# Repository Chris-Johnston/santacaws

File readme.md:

# Santa CAWs

More novelty circuitboards, powered by an ATTINY404.

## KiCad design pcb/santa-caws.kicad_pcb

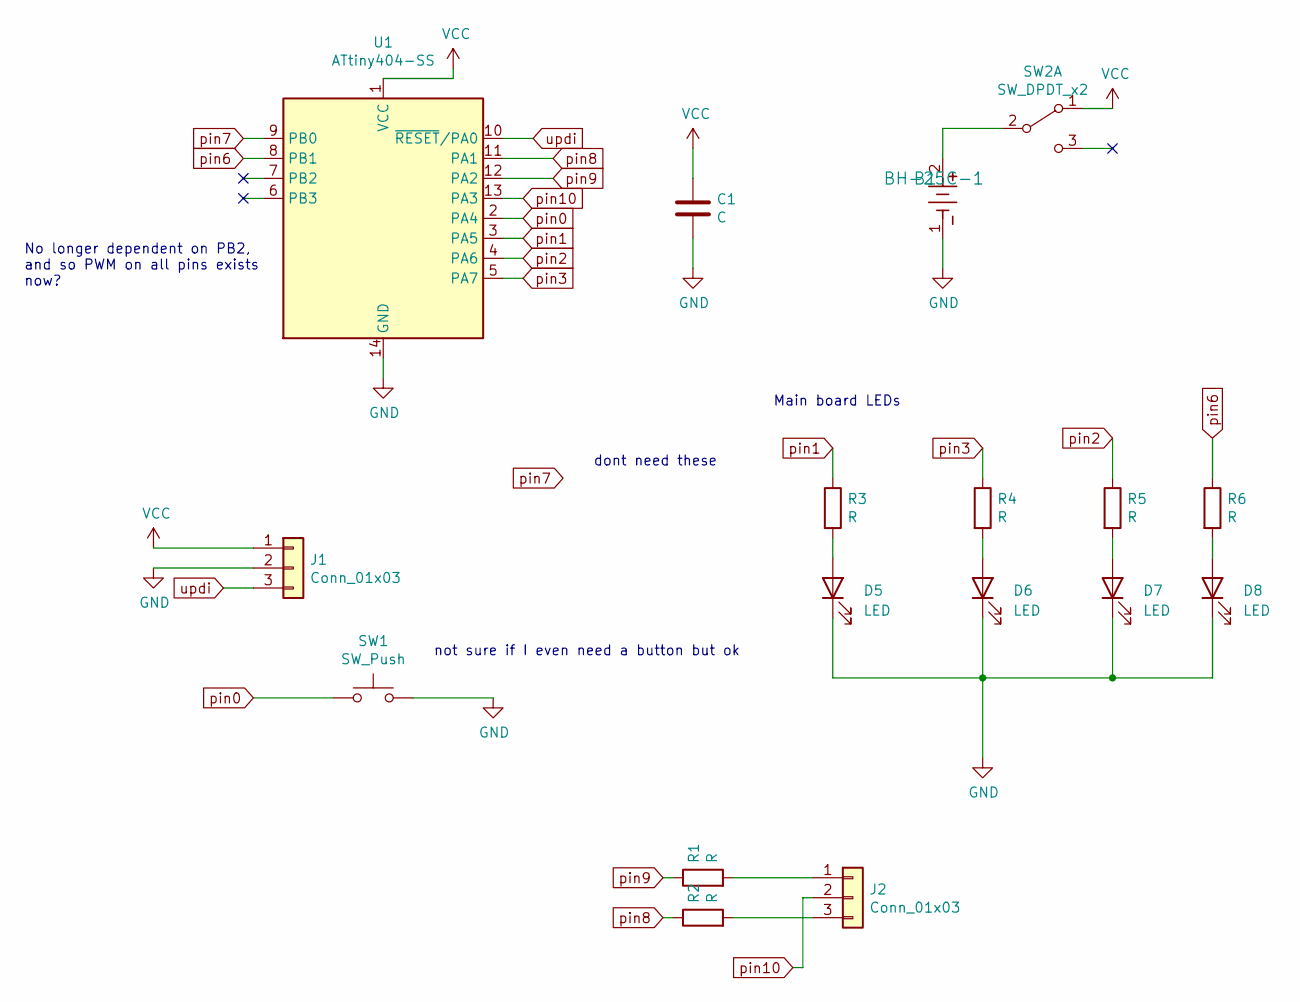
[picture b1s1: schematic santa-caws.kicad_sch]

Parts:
B1: BH-25C-1; BH-25C-1_ADM
C1: C; C_1206_3216Metric_Pad1.33x1.80mm_HandSolder
D5, D6, D7, D8: LED; Custom_LessSilkscreenLED_1206_3216Metric_Pad1.42x1.75mm_Han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
J1: Conn_01x03; custom_updipad_PinHeader_1x03_P2.54mm_Vertical
J2: Conn_01x03; PinSocket_1x03_P2.54mm_Horizontal
R1, R2, R3, R4, R5, R6: R; R_1206_3216Metric_Pad1.30x1.75mm_HandSolder
SW1: SW_Push; SW_Push_1P1T_NO_6x6mm_H9.5mm
SW2: SW_DPDT_x2; SW_SPDT_CK-JS102011SAQN
U1: ATtiny404-SS; SOIC-14_3.9x8.7mm_P1.27mm

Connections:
GND: B1.1, C1.2, D5.1 (K), D6.1 (K), D7.1 (K), D8.1 (K), J1.2, SW1.2, U1.14 (GND)
unnamed: B1.2, SW2.2 (B)
unnamed: D5.2 (A), R3.2
unnamed: D6.2 (A), R4.2
unnamed: D7.2 (A), R5.2
unnamed: D8.2 (A), R6.2
unnamed: J2.1, R1.2
unnamed: J2.3, R2.2
VCC: C1.1, J1.1, SW2.1 (A), U1.1 (VCC)
pin0: SW1.1, U1.2 (PA4)
pin1: R3.1, U1.3 (PA5)
pin2: R5.1, U1.4 (PA6)
pin3: R4.1, U1.5 (PA7)
pin6: R6.1, U1.8 (PB1)
pin7: U1.9 (PB0)
pin8: R2.1, U1.11 (PA1)
pin9: R1.1, U1.12 (PA2)
pin10: J2.2, U1.13 (PA3)
updi: J1.3, U1.10 (~RESET/PA0)

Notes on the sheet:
not sure if I even need a button but ok
No longer dependent on PB2, and so PWM on all pins exists now?
dont need these
Main board LEDs

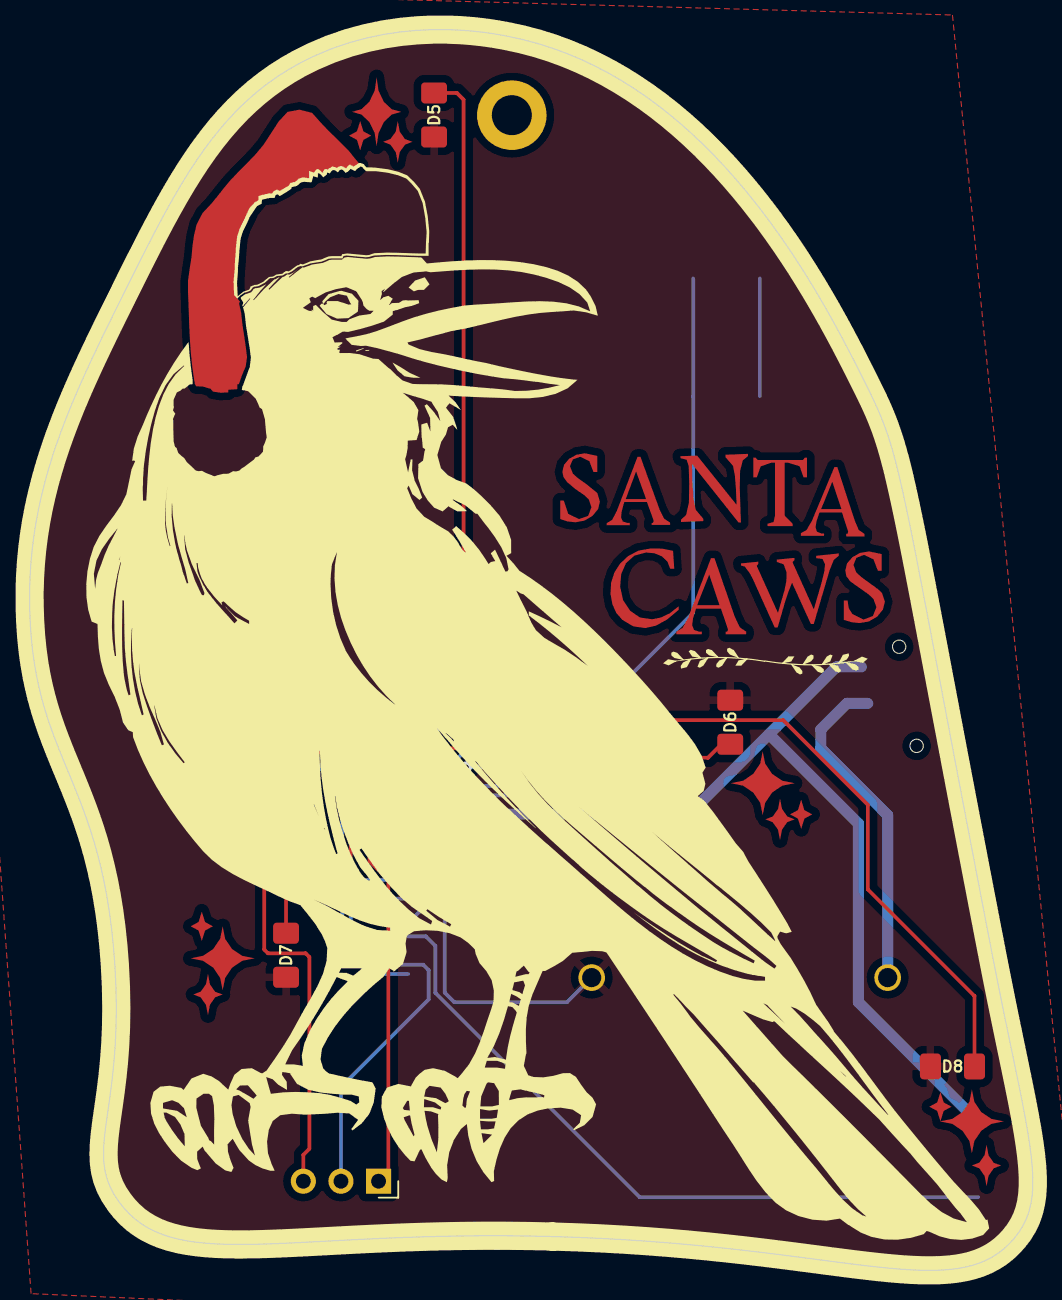
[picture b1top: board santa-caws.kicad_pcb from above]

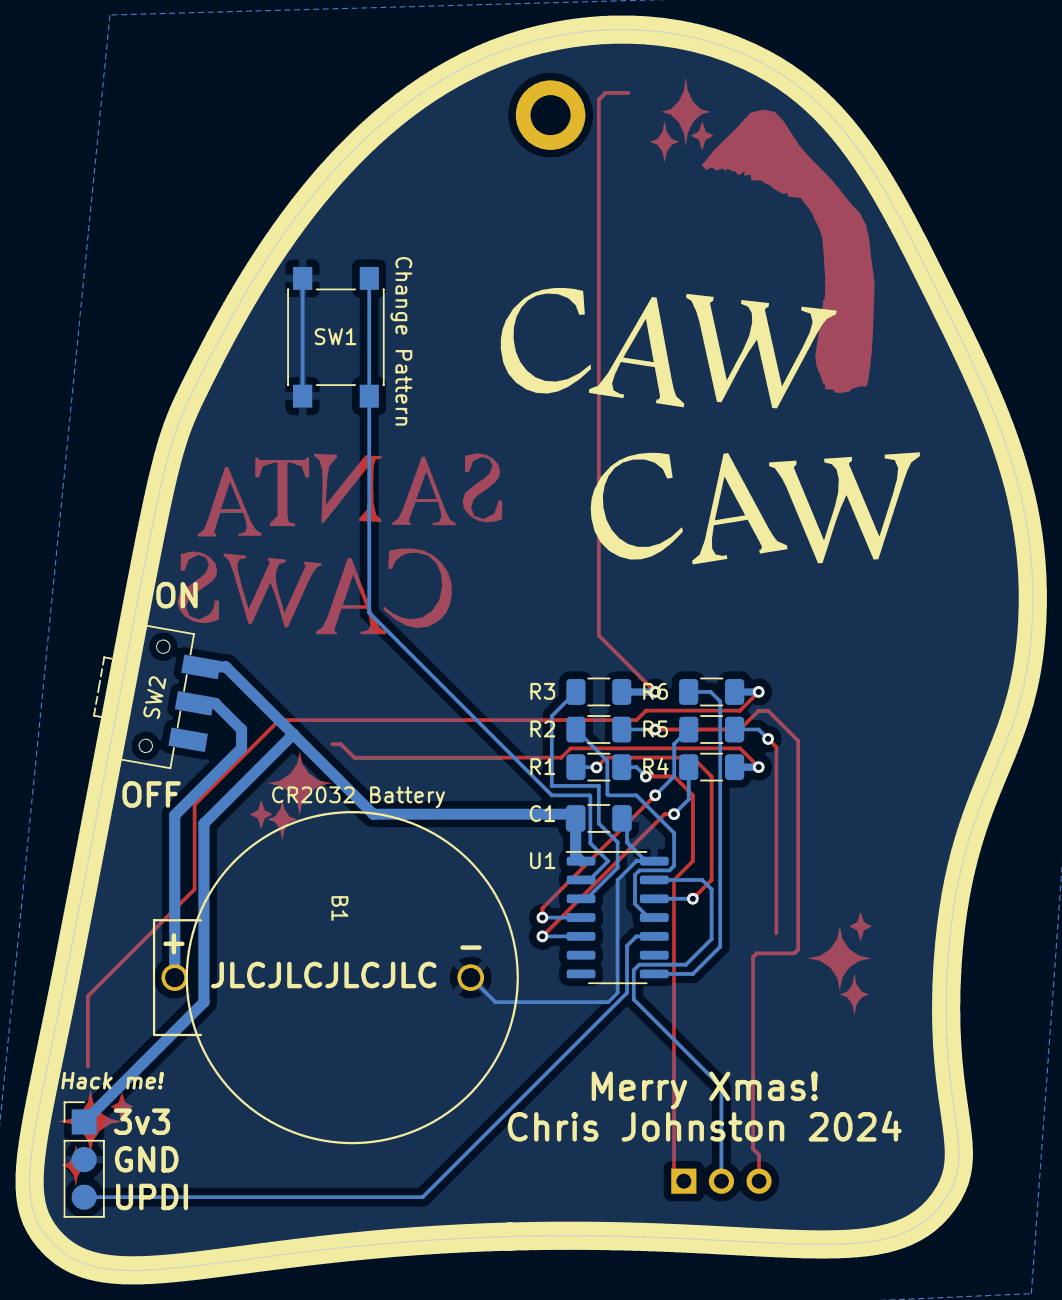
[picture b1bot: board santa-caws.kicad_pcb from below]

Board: 2 copper layers, 67.8 x 83.8 mm, 18 parts (12 on the bottom side), 18 nets.

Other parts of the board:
svg2mod: G***; santa-caws_128dpi

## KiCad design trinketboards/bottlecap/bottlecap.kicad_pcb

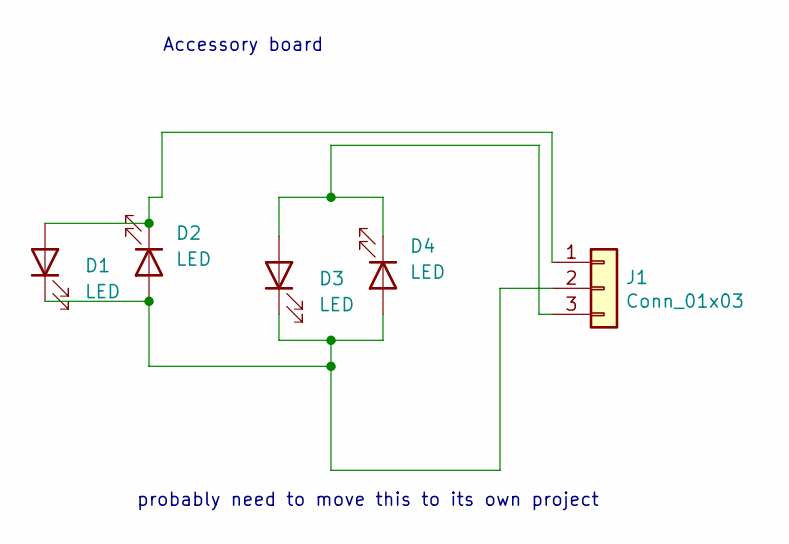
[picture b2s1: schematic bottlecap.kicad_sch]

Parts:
D1, D2, D3, D4: LED; Custom_LessSilkscreenLED_1206_3216Metric_Pad1.42x1.75mm_Han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
J1: Conn_01x03; PinHeader_1x03_P2.54mm_Horizontal

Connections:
unnamed: D1.1 (K), D2.2 (A), D3.1 (K), D4.2 (A), J1.2
unnamed: D1.2 (A), D2.1 (K), J1.1
unnamed: D3.2 (A), D4.1 (K), J1.3

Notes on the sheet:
probably need to move this to its own project
Accessory board

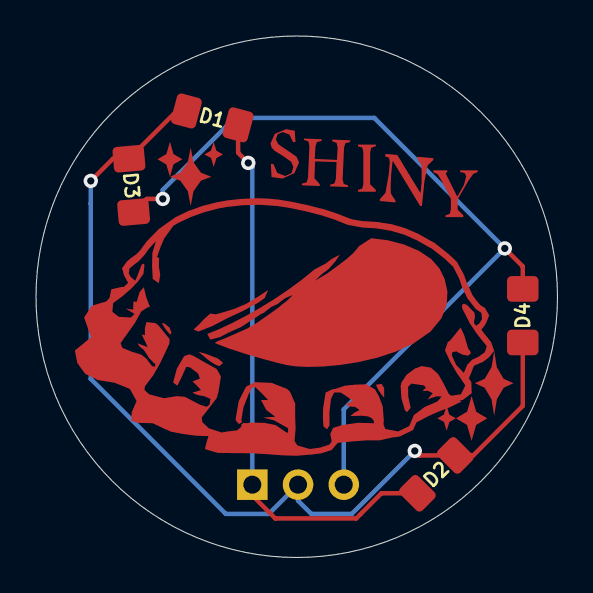
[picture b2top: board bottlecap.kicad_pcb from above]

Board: 2 copper layers, 29.0 x 29.0 mm, 6 parts (1 on the bottom side), 3 nets.

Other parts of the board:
svg2mod: G***; trinket-bottlecap-inkscape

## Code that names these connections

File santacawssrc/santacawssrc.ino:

// santa caws 

// this is super-duper messy because I've been busy and then sick

#include <avr/io.h>
#include <avr/interrupt.h>
#include <util/delay.h>
#include <avr/pgmspace.h>

#include <pins_arduino.h>

// #define PIN_OUTPUT_COUNT 10
#define PIN_BUTTON PIN_PA4

#undef MILLIS_USE_TIMERB0 

#define DEBOUNCE_TIME 75

#define CORRECTED_MILLIS (millis())
#define CORRECTED_DELAY(ms) (delay(ms))

void blinkPattern();
void fhqwhgadsPattern();
void fadeoutPattern();
void secretMessagePattern();
void spinPattern();
void clockPattern();

typedef void (*PatternFunction)();

PatternFunction patternList[] = {
  fhqwhgadsPattern,
  
  spinPattern,
  
  blinkPattern,
  clockPattern,
  
  fadeoutPattern,
  secretMessagePattern,
};

#define NUM_PATTERNS (sizeof(patternList) / sizeof(PatternFunction))

int mainboardPins[] = {
  // 1, 3, 2, 6
  PIN_PA5, PIN_PA7, PIN_PA6, PIN_PB1
};

int swPwmPins[] = {
  PIN_PA5, PIN_PA7, PIN_PA6, PIN_PB1,
  PIN_PA3, PIN_PA1, PIN_PA2,
};

#define COUNT_PWM_PINS 7
#define ALL_PINS_LEN 7

#define MAINBOARD_PINS_LENGTH 4

int childboardCommon = PIN_PA3; // 10
int childboardLeft = PIN_PA1; // 8
int childboardRight = PIN_PA2; // 9

unsigned long lastDebounceTime = 0;
int pattern = 0;

uint8_t pwmTimers[COUNT_PWM_PINS] = {0};
bool pwmTimersEnabled[COUNT_PWM_PINS] = {0};
int pwmTimer = 0;

void setupIsr();

// the setup function runs once when you press reset or power the board
void setup() {
  
  for (int i = 0; i < COUNT_PWM_PINS; i++)
  {
    pinMode(swPwmPins[i], OUTPUT);
  }
  // pinMode(childboardCommon, OUTPUT);
  // pinMode(childboardLeft, OUTPUT);
  // pinMode(childboardRight, OUTPUT);

  pinMode(PIN_BUTTON, INPUT_PULLUP);

  setupIsr();
}

int lastButtonState = 0;
int buttonState = 0;

#define TCB0_CTRLA_ENABLE 1
#define TCB0_CTRLA_CLKSEL_1 0 // CLK_PER
#define TCB0_CTRLA_CLKSEL_half 1 // CLK_PER / 2
#define TCB0_CTRLB_ASYNC 0b01000000
#define TCB0_CTRLB_PERIODIC_INTERRUPT_MODE 0b00

void setupIsr() {
  TCB0.CCMP = 0xfff;
  TCB0.CTRLB = TCB0_CTRLB_ASYNC | TCB0_CTRLB_PERIODIC_INTERRUPT_MODE;
  TCB0.INTCTRL = 1 ; // no capture interrupt
  TCB0.CTRLA = TCB0_CTRLA_CLKSEL_1 | TCB0_CTRLA_ENABLE;
  
  // pin 2 interrupt
  // bit 7 invert I/O
  // pull up enabled (bit 3)
  // bits 2:0 - sense falling edge
  // PORTA_PIN2CTRL = 0b1000 | 0x3;

  // button is on pin a4
  // TODO TODO check these flags
  PORTA.INTFLAGS = (1 << 4);// 0b100;
  PORTA.PIN4CTRL = 0b10000000 | 0b1000 | 0b11;
  VPORTA.INTFLAGS = (1 << 4);
  // PORTA.INTCTRL = 1;
  // PORTA.PIN2CTRL = 0b1011;
}
void setPwm(int pin, bool pwmEnabled, int pwmRate)
{
  pwmTimersEnabled[pin] = pwmEnabled;
  if (pwmEnabled)
  {
    pwmTimers[pin] = pwmRate & 255;
  }
  else {
    pwmTimers[pin] = 0;
  }
}

bool isporta(int pin) {

  // only pin PB1 is used 
  // return pin != PIN_PB0
  // if (pin < PIN_PB0 && pin > PIN_PB3) {
  if (pin == PIN_PB1) {
    return false;
  }
  return true;
}

ISR(TCB0_INT_vect) {

  pwmTimer = (pwmTimer + 1) % 255;
  uint8_t portASet = 0, portAClear = 0;
  uint8_t portBSet = 0, portBClear = 0;
  
  for (int i = 0; i < COUNT_PWM_PINS; i++) {
    // preserve whatevers already in the register
    if (pwmTimersEnabled[i] == false) continue;

    // not sure this will work with the common childboard, dunno
    int swPwmPin = swPwmPins[i];
    
    if (pwmTimer < pwmTimers[i]) {

      // this was annoying
      if (isporta(swPwmPin)) {
        portASet |= digital_pin_to_bit_mask[swPwmPin];
      } else {
        portBSet |= digital_pin_to_bit_mask[swPwmPin];
      }
    }
    else {
      if (isporta(swPwmPin)) {
        portAClear |= digital_pin_to_bit_mask[swPwmPin];
      } else {
        portBClear |= digital_pin_to_bit_mask[swPwmPin];
      }
    }
  }

  PORTA.OUTSET = portASet;
  PORTA.OUTCLR = portAClear;
  PORTB.OUTSET = portBSet;
  PORTB.OUTCLR = portBClear;

  TCB0.INTFLAGS = 0; // clear interrupt
}

ISR(PORTA_PORT_vect) {
  byte flags = PORTA.INTFLAGS;
  PORTA.INTFLAGS |= flags;
  
  if ((CORRECTED_MILLIS - lastDebounceTime) > DEBOUNCE_TIME) {

    pattern = (pattern + 1) % NUM_PATTERNS;
    clear();

    lastDebounceTime = CORRECTED_MILLIS;
  }
}

// anything beyond this is too dang bright
// #define MAX_PWM_BRIGHTNESS 75

void clearPwm() {
  for (int i = 0; i < COUNT_PWM_PINS; i++) {
    setPwm(i, false, 0);
  }
}

void clear()
{
  clearPwm();
  PORTA.OUT = 0;
  PORTB.OUT = 0;
}

void loop() {
  int lastPattern = pattern;
  (*patternList[lastPattern])();

  // pattern has changed
  if (pattern != lastPattern) {
    clear();
  }

  delay(50); // doesn't need to spin super duper fast
}

// void clockPattern() {
//   // clear();
//   int time = ((int)(CORRECTED_MILLIS / 1000));

//   for (int i = 0; i < MAINBOARD_PINS_LENGTH; i++) {
//     bool b = time & (1 << i);
//     digitalWrite(mainboardPins[i], b > 0);
//   }
// }

void clockPattern() {
  // clear();
  int time = ((int)(CORRECTED_MILLIS / 1000));

  for (int i = 0; i < MAINBOARD_PINS_LENGTH; i++) {
    bool b = time & (1 << i);
    digitalWrite(mainboardPins[i], b > 0);
  }
}

int vSpinPatternLUT[] = {0, 50, 255, 128 };

void spinPattern() {

   int offset = (int)(CORRECTED_MILLIS / 100.0) % MAINBOARD_PINS_LENGTH;

  for (int i = 0; i < MAINBOARD_PINS_LENGTH; i++) {
    setPwm(i, true, vSpinPatternLUT[(i + offset) % MAINBOARD_PINS_LENGTH]);
  }
}

void fadeoutPattern() {
  int r = rand() % MAINBOARD_PINS_LENGTH;

  setPwm(swPwmPins[r], true, 255);

  for (int i = 0; i < COUNT_PWM_PINS; i++) {
    pwmTimers[i] *= 0.75;
  }

  delay(rand() % 100);
}

void allOff() {
  for (int i = 0; i < MAINBOARD_PINS_LENGTH; i++) {
    digitalWrite(mainboardPins[i], LOW);
  }

  digitalWrite(childboardCommon, 0);
  digitalWrite(childboardLeft, 0);
  digitalWrite(childboardRight, 0);
}

void allOn() {
  for (int i = 0; i < MAINBOARD_PINS_LENGTH; i++) {
    digitalWrite(mainboardPins[i], HIGH);
  }
}

bool blinkState = false;
void blinkPattern() {
  for (int i = 0; i < MAINBOARD_PINS_LENGTH; i++) {
    // mainboardPins
    // PIN_PA5, PIN_PA7, PIN_PA6, PIN_PB1
    digitalWrite(mainboardPins[i], blinkState);
  }
  digitalWrite(childboardCommon, blinkState);
  digitalWrite(childboardLeft, !blinkState);
  digitalWrite(childboardRight, !blinkState);
  delay(500);
  blinkState = !blinkState;
}

void fhqwhgadsPattern() {

  allOff();
  delay(50 + rand() % 500);

  int r = rand() % 4;
  bool mainboard = (rand() % 2) == 1;

  if (mainboard) {
    digitalWrite(mainboardPins[r], HIGH);
  } else {

    digitalWrite(childboardCommon, (r/2) == 1);
    digitalWrite(childboardLeft, (r % 2) == 0);
    digitalWrite(childboardLeft, (r % 2) == 1);

  }

  delay(20 + rand() % 50);
}

void showNibble(int nibble) {
  allOff();
  for (int i = 0; i < MAINBOARD_PINS_LENGTH; i++) {
    bool b = nibble & (1 << i);
    digitalWrite(mainboardPins[i], b);
  }
}

void secretMessagePattern() {
  for (int j = 0; j < 3; j++) {
    for (int i = 0; i < MAINBOARD_PINS_LENGTH; i++) {
      allOff();
      digitalWrite(mainboardPins[i], HIGH);
      delay(100);
      allOff();
      delay(100);
    }
    delay(200);
  }

  const char message[] = "secret=Y'all ever just yeet?? Lmao";
  const int len = 28;

  for (int i = 0; i < len; i++) {
    // should alternate the daughterboard so that timing is more clear
    // upper nibble
    showNibble(message[i] >> 4);
    delay(100);

    // lower nibble
    showNibble(message[i]);
    delay(100);
  }

  for (int i = 0; i < 5; i++) {
    allOff();
    delay(100);
    allOn();
    delay(100);
  }
}

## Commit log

2025-02-22 calling this as good enough
2025-03-08 update build docs
2025-03-08 add more screenshots
2025-03-08 oops
